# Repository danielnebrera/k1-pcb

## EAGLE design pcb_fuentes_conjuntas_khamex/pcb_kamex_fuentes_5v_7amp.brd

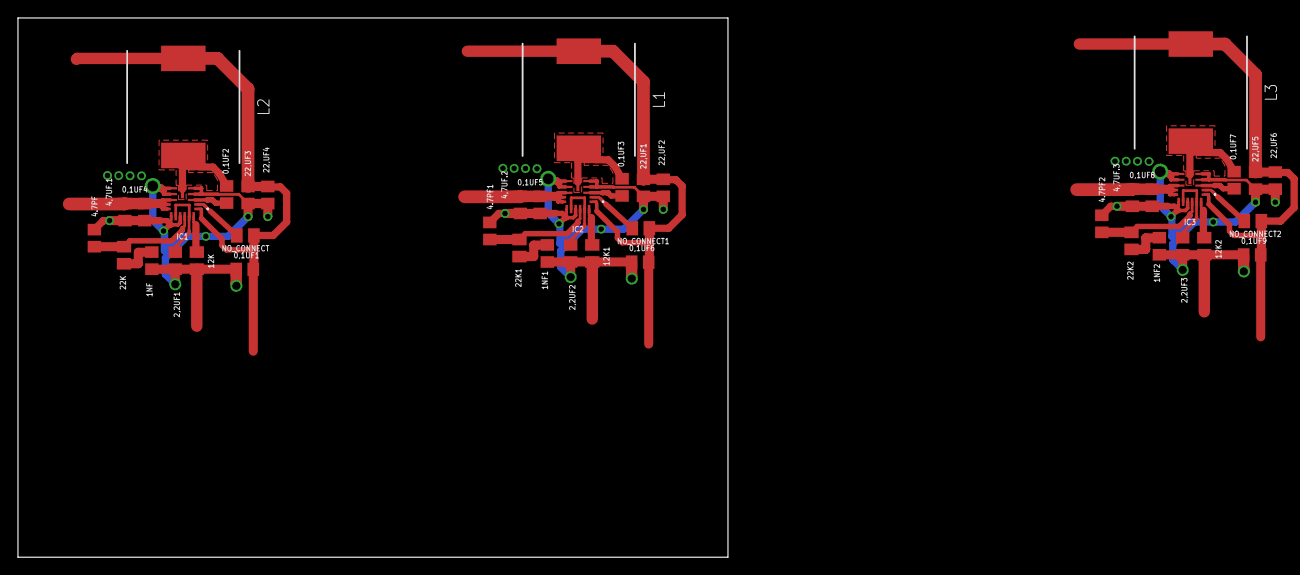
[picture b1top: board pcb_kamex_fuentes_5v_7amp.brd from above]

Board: 2 copper layers, 79.0 x 60.0 mm, 42 parts (0 on the bottom side), 26 nets.

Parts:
0,1UF1, 0,1UF2, 0,1UF3, 0,1UF4, 0,1UF5, 0,1UF6, 0,1UF7, 0,1UF8, 0,1UF9: 0.1uF_50-V; C0805
1NF, 1NF1, 1NF2: 1nf_50-V; C0805
2,2UF1, 2,2UF2, 2,2UF3: 2,2uf_10-V; C0805
4,7UF.1, 4,7UF.2, 4,7UF.3: 4,7uf_50-V; C0805
4.7PF, 4.7PF1, 4.7PF2: 4.7pf_50-V; C0805
12K, 12K1, 12K2: 12k_50v; M0805
22,UF1, 22,UF2, 22,UF3, 22,UF4, 22,UF5, 22,UF6: 22uf_10-V; C0805
22K, 22K1, 22K2: 22k_50v; M0805
IC1, IC2, IC3: MAX20008AFOC_VY+T; MAX20008AFOCVYT
L1, L2, L3: DR125-1R0-R; INDPM125125X600N
NO_CONNECT, NO_CONNECT1, NO_CONNECT2: 10k_50-V; M0805

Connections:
BIAS: 2,2UF1.1, IC1.13, IC1.16
BIAS1: 2,2UF2.1, IC2.13, IC2.16
BIAS2: 2,2UF3.1, IC3.13, IC3.16
BST: 0,1UF2.2, IC1.3
BST1: 0,1UF3.2, IC2.3
BST2: 0,1UF7.2, IC3.3
COM: 4.7PF.1, 22K.1, IC1.15
COM1: 4.7PF1.1, 22K1.1, IC2.15
COM2: 4.7PF2.1, 22K2.1, IC3.15
GND: 0,1UF1.1, 0,1UF4.1, 0,1UF5.1, 0,1UF6.1, 0,1UF8.1, 0,1UF9.1, 1NF.1, 1NF1.1, 1NF2.1, 2,2UF1.2, 2,2UF2.2, 2,2UF3.2, 4,7UF.1.1, 4,7UF.2.1, 4,7UF.3.1, 4.7PF.2, 4.7PF1.2, 4.7PF2.2, 12K.2, 12K1.2, 12K2.2, 22,UF1.1, 22,UF2.1, 22,UF3.1, 22,UF4.1, 22,UF5.1, 22,UF6.1, IC1.4, IC1.5, IC1.7, IC1.8, IC1.12, IC1.14, IC2.4, IC2.5, IC2.7, IC2.8, IC2.12, IC2.14, IC3.4, IC3.5, IC3.7, IC3.8, IC3.12, IC3.14
unnamed: 12K1.1, IC2.17
unnamed: 1NF.2, 22K.2
unnamed: 0,1UF3.1, IC2.6, L1.1
unnamed: IC2.2, NO_CONNECT1.1
unnamed: 1NF1.2, 22K1.2
unnamed: 12K.1, IC1.17
unnamed: 12K2.1, IC3.17
unnamed: 0,1UF7.1, IC3.6, L3.1
unnamed: 0,1UF2.1, IC1.6, L2.1
unnamed: IC1.2, NO_CONNECT.1
unnamed: IC3.2, NO_CONNECT2.1
unnamed: 1NF2.2, 22K2.2
VIN_12V: 0,1UF4.2, 0,1UF5.2, 0,1UF8.2, 4,7UF.1.2, 4,7UF.2.2, 4,7UF.3.2, IC1.9, IC1.10, IC1.11, IC2.9, IC2.10, IC2.11, IC3.9, IC3.10, IC3.11
VOUT_5V: 0,1UF1.2, 22,UF3.2, 22,UF4.2, IC1.1, L2.2, NO_CONNECT.2
VOUT_5V1: 0,1UF6.2, 22,UF1.2, 22,UF2.2, IC2.1, L1.2, NO_CONNECT1.2
VOUT_5V2: 0,1UF9.2, 22,UF5.2, 22,UF6.2, IC3.1, L3.2, NO_CONNECT2.2

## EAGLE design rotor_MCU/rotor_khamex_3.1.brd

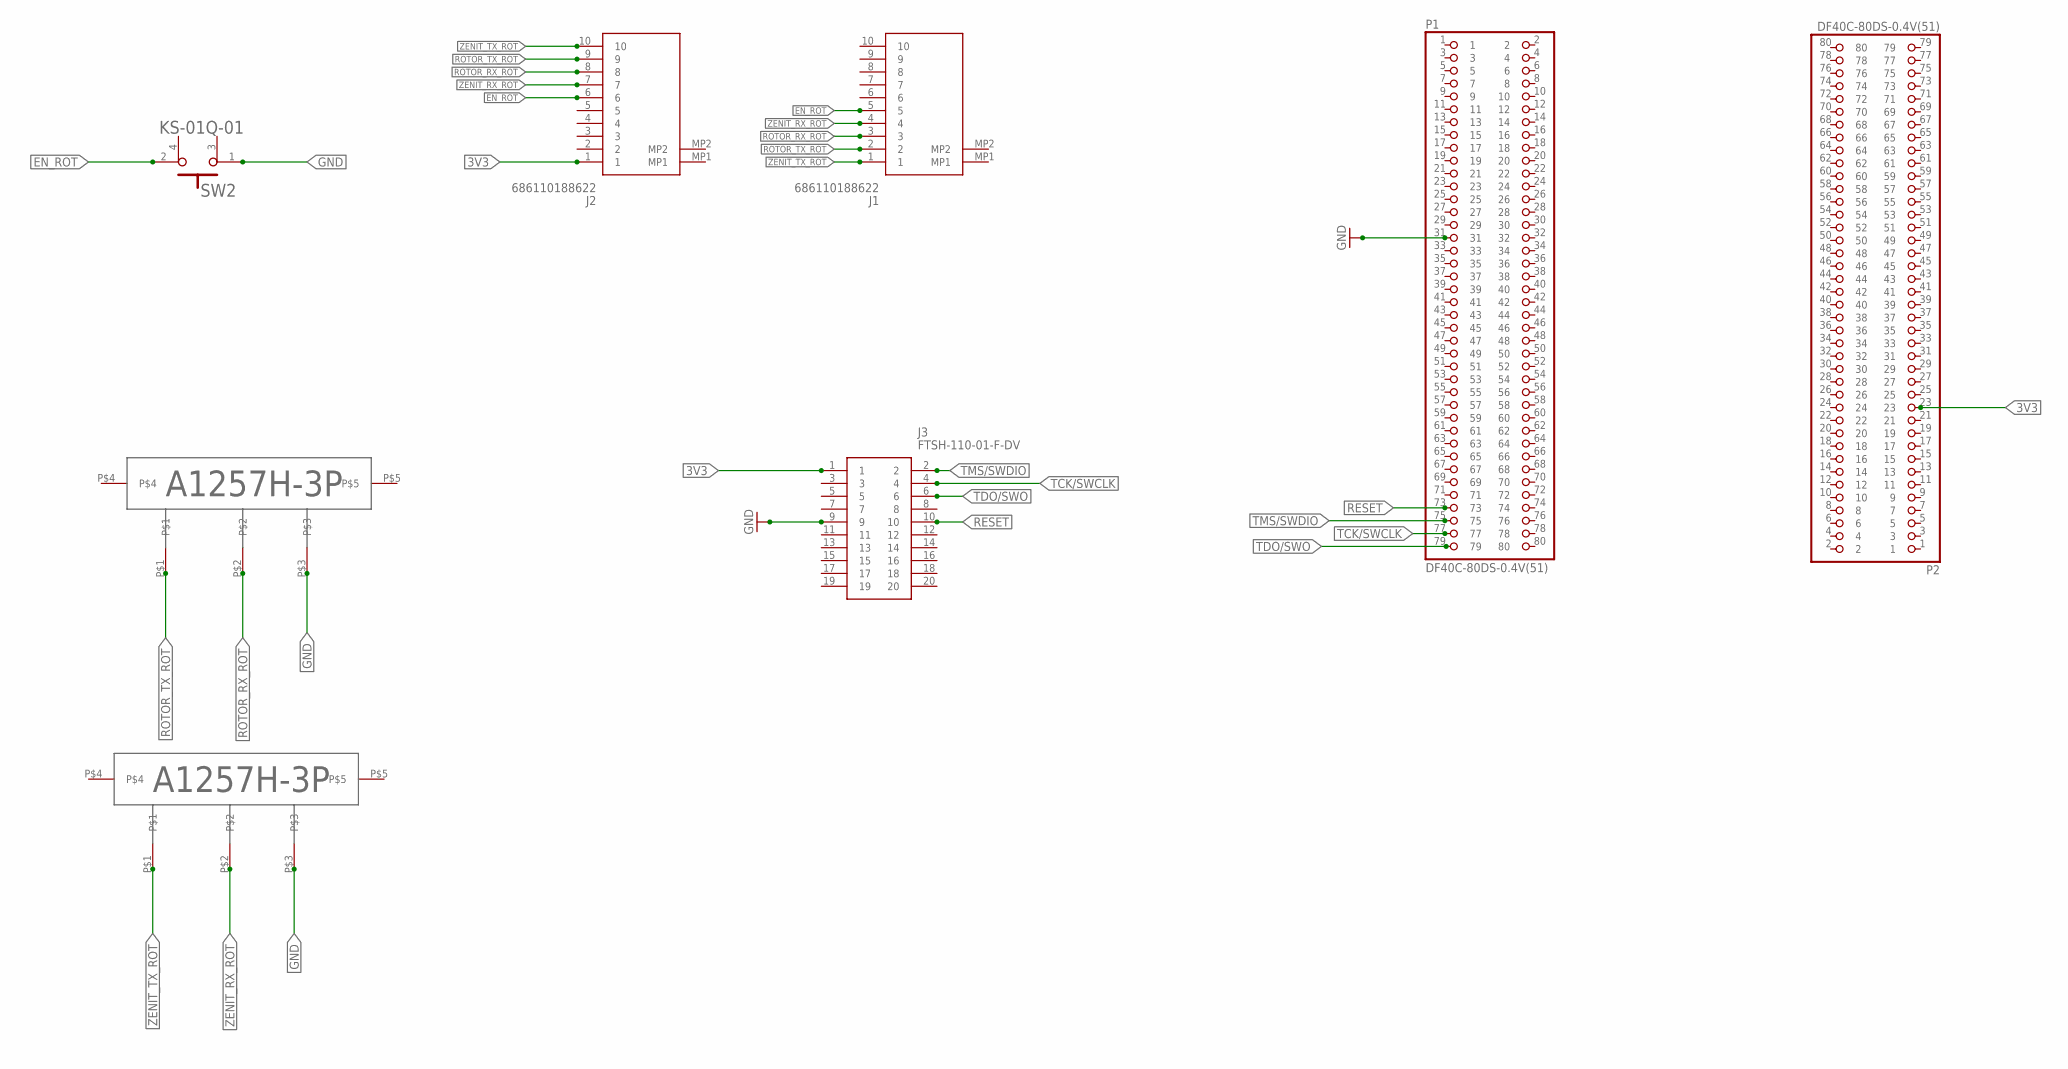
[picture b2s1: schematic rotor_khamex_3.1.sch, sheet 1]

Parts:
J1, J2: 686110188622
J3: FTSH-110-01-F-DV; FTSH-110-XX-YYY-DV
MOTOR_ROTOR: A1257H-3P_DEVICE; A1257H-3P_PACK
MOTOR_ZENIT: A1257H-3P_DEVICE; A1257H-3P_PACK
P1, P2: DF40C-80DS-0.4V(51); HRS_DF40C-80DS-0.4V(51)
SW2: E-SWITCH_KS-01Q-01E-SWITCH_KS-01Q-01_0_0; E-SWITCH_KS-01Q-01_0

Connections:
3V3: J2.1, J3.1, P2.23
EN_ROT: J1.5, J2.6, SW2.2
GND: J3.9, MOTOR_ROTOR.P$3, MOTOR_ZENIT.P$3, P1.31, SW2.1; also elsewhere on the board
RESET: J3.10, P1.73
ROTOR_RX_ROT: J1.3, J2.8, MOTOR_ROTOR.P$2
ROTOR_TX_ROT: J1.2, J2.9, MOTOR_ROTOR.P$1
TCK/SWCLK: J3.4, P1.77
TDO/SWO: J3.6
TMS/SWDIO: J3.2, P1.75
ZENIT_RX_ROT: J1.4, J2.7, MOTOR_ZENIT.P$2
ZENIT_TX_ROT: J1.1, J2.10, MOTOR_ZENIT.P$1

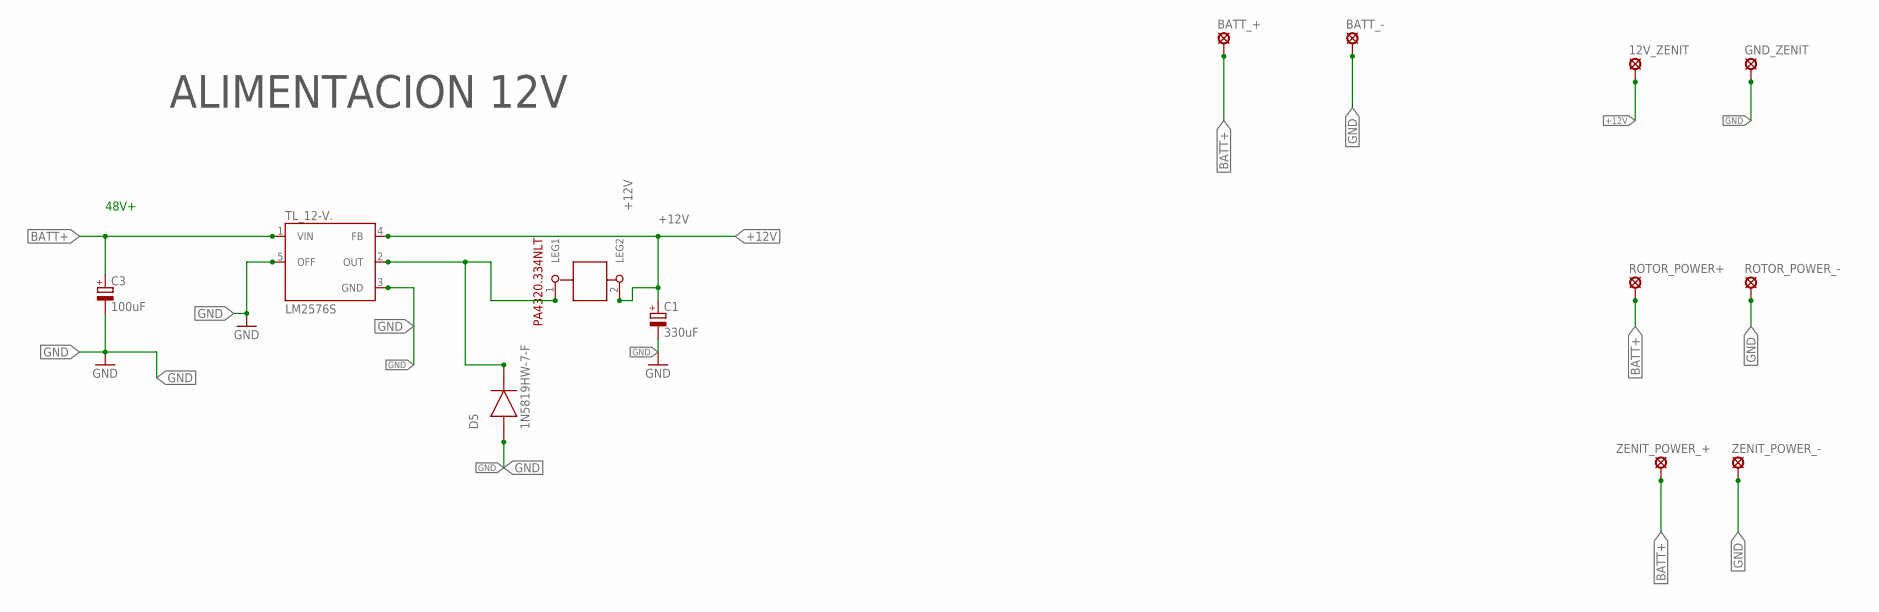
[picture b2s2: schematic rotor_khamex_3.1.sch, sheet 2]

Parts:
12V_ZENIT: SE14
BATT_+: SE14
BATT_-: SE14
C1: 330uF; E5-10,5
C3: 100uF; E5-10,5
D5: 1N5819HW-7-F; SOD370155X135
GND_ZENIT: SE14
L: 1212; 1212SMDINDUCTORPACK
ROTOR_POWER+: SE14
ROTOR_POWER_-: SE14
TL_12-V.: LM2576S; TO263-5
ZENIT_POWER_+: SE14
ZENIT_POWER_-: SE14

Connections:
+12V: 12V_ZENIT.MP, C1.+, L.2 (LEG2), TL_12-V..4 (FB)
BATT+: BATT_+.MP, C3.+, ROTOR_POWER+.MP, TL_12-V..1 (VIN), ZENIT_POWER_+.MP
GND: BATT_-.MP, C1.-, C3.-, D5.2 (A), GND_ZENIT.MP, ROTOR_POWER_-.MP, TL_12-V..3 (GND), TL_12-V..5 (OFF), ZENIT_POWER_-.MP; also elsewhere on the board
unnamed: D5.1 (C), L.1 (LEG1), TL_12-V..2 (OUT)

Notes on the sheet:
48V+
ALIMENTACION 12V

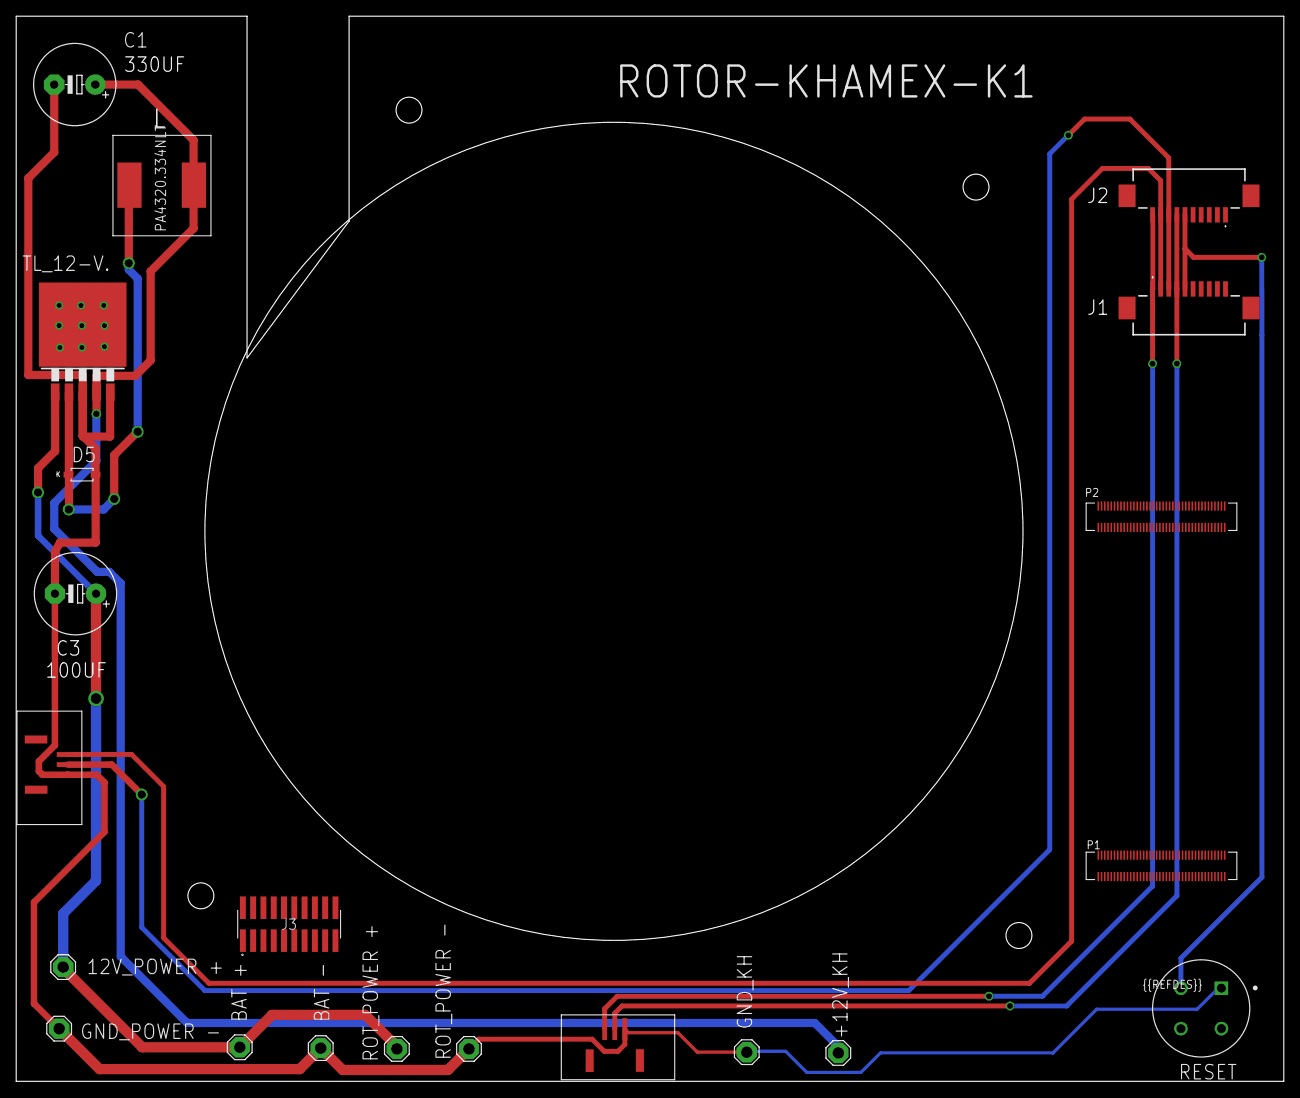
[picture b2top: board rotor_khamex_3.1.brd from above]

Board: 4 copper layers, 156.5 x 131.5 mm, 21 parts (0 on the bottom side), 13 nets.

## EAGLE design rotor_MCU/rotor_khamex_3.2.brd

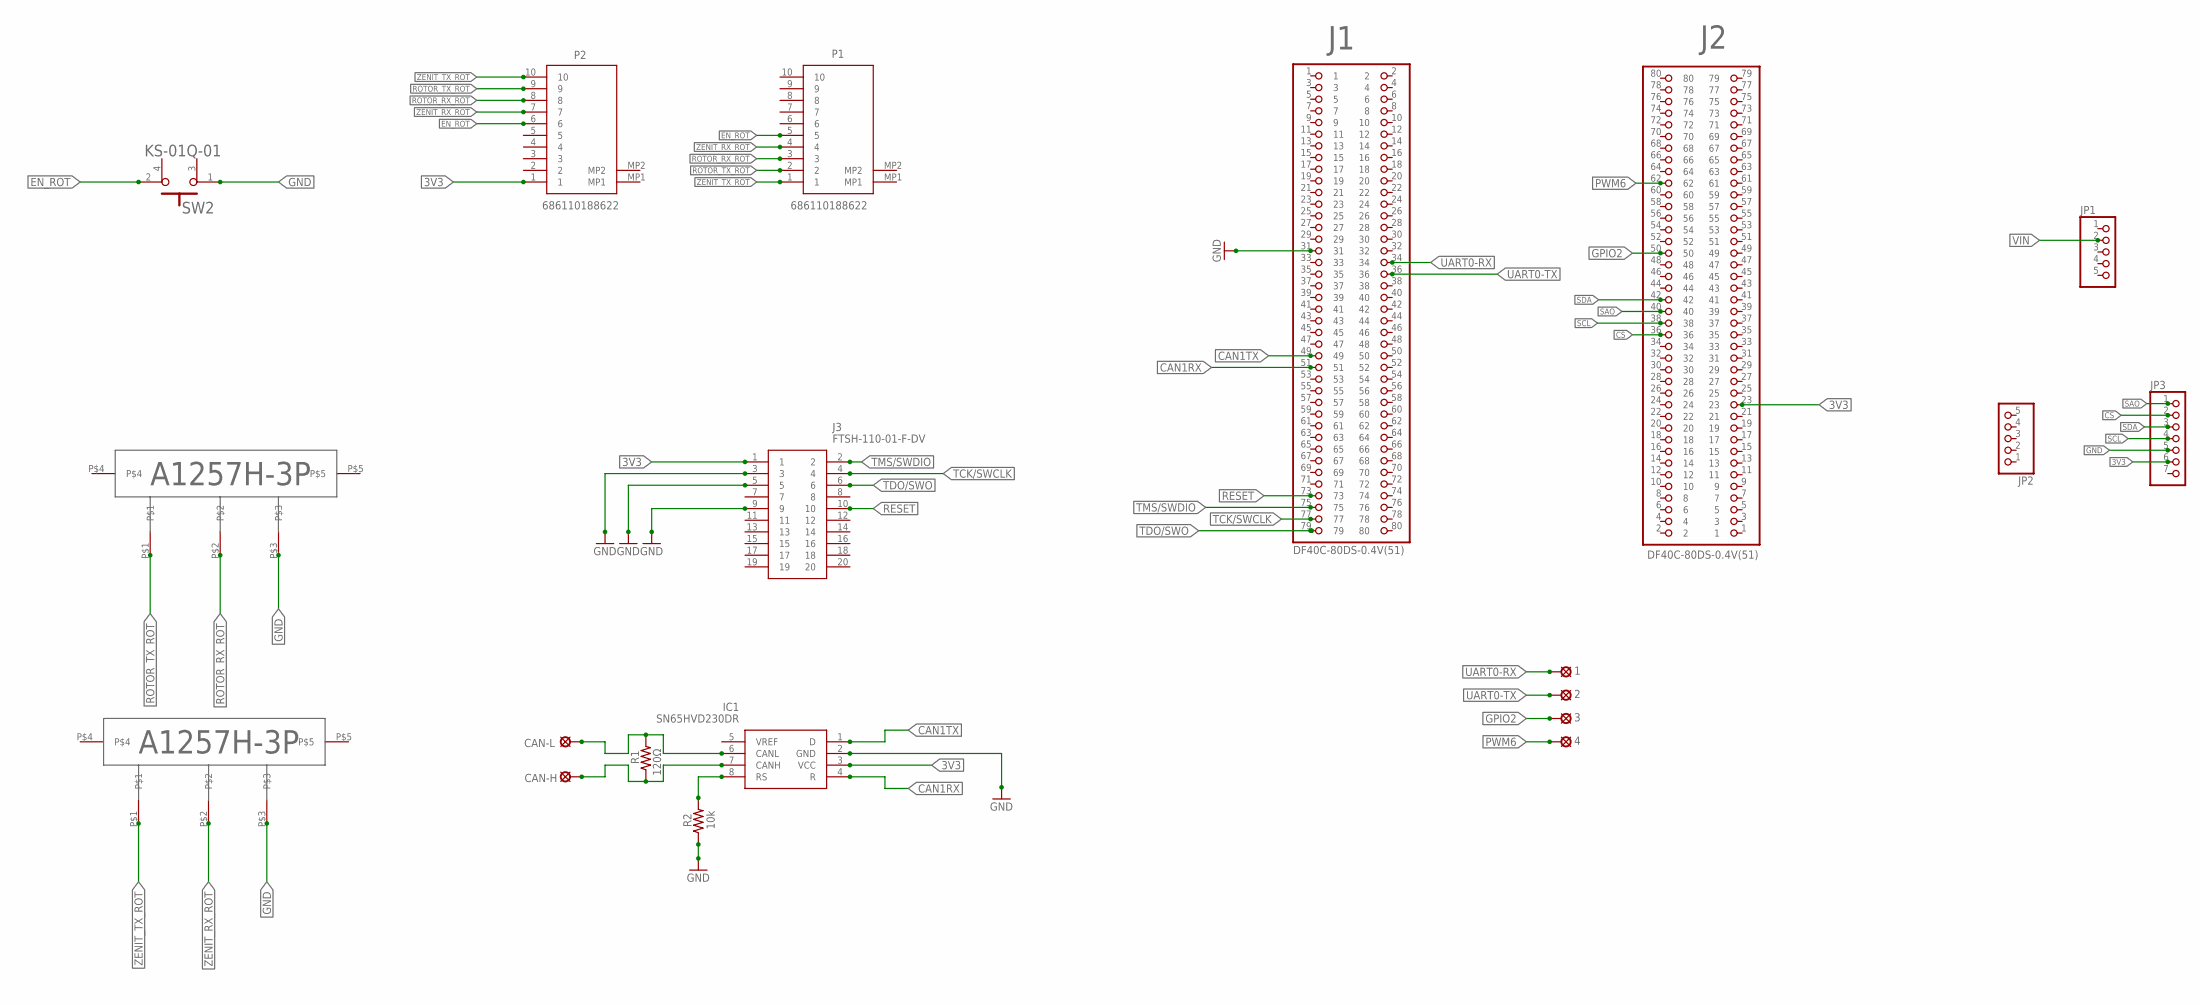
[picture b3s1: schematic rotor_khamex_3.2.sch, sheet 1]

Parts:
1, 2, 3, 4: LSP11
CAN-H: LSP11
CAN-L: LSP11
IC1: SN65HVD230DR; SOT127P600X175-8N
J1, J2: DF40C-80DS-0.4V(51); HRS_DF40C-80DS-0.4V(51)
J3: FTSH-110-01-F-DV; FTSH-110-XX-YYY-DV
JP1, JP2: PINHD-1X5; 1X05
JP3: PINHD-1X7; 1X07
MOTOR_ROTOR: A1257H-3P_DEVICE; A1257H-3P_PACK
MOTOR_ZENIT: A1257H-3P_DEVICE; A1257H-3P_PACK
P1, P2: 686110188622
R1: 120Ω; M0805
R2: 10k; M0805
SW2: E-SWITCH_KS-01Q-01E-SWITCH_KS-01Q-01_0_0; E-SWITCH_KS-01Q-01_0

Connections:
3V3: IC1.3 (VCC), J2.23, J3.1, JP3.6, P2.1
CAN1RX: IC1.4 (R), J1.51
CAN1TX: IC1.1 (D), J1.49
CS: J2.36, JP3.2
EN_ROT: P1.5, P2.6, SW2.2; also elsewhere on the board
GND: IC1.2 (GND), J1.31, J3.3, J3.5, J3.9, JP3.5, MOTOR_ROTOR.P$3, MOTOR_ZENIT.P$3, R2.1, SW2.1; also elsewhere on the board
GPIO2: 3.MP, J2.50
unnamed: CAN-H.MP, IC1.7 (CANH), R1.1
unnamed: CAN-L.MP, IC1.6 (CANL), R1.2
unnamed: IC1.8 (RS), R2.2
PWM6: 4.MP, J2.62
RESET: J1.73, J3.10
ROTOR_RX_ROT: MOTOR_ROTOR.P$2, P1.3, P2.8
ROTOR_TX_ROT: MOTOR_ROTOR.P$1, P1.2, P2.9
SAO: J2.40, JP3.1
SCL: J2.38, JP3.4
SDA: J2.42, JP3.3
TCK/SWCLK: J1.77, J3.4
TDO/SWO: J1.79, J3.6
TMS/SWDIO: J1.75, J3.2
UART0-RX: 1.MP, J1.34
UART0-TX: 2.MP, J1.36
VIN: JP1.2
ZENIT_RX_ROT: MOTOR_ZENIT.P$2, P1.4, P2.7
ZENIT_TX_ROT: MOTOR_ZENIT.P$1, P1.1, P2.10

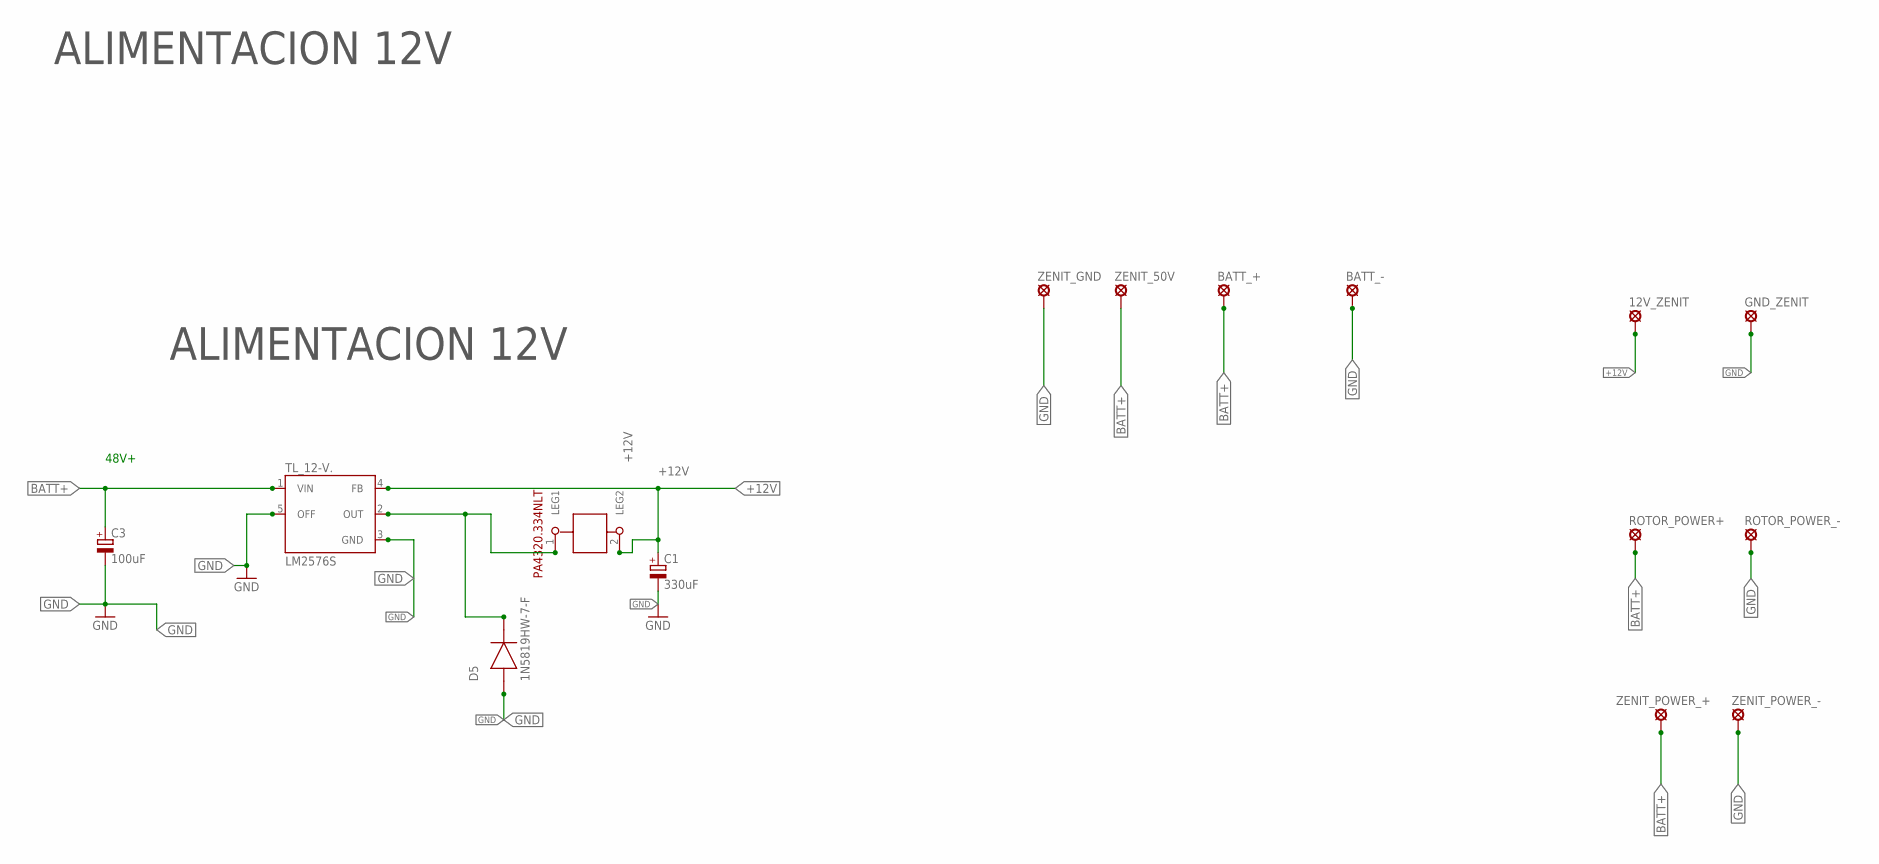
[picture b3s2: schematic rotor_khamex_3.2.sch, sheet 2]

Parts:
12V_ZENIT: SE14
BATT_+: SE14
BATT_-: SE14
C1: 330uF; E5-10,5
C3: 100uF; E5-10,5
D5: 1N5819HW-7-F; SOD370155X135
GND_ZENIT: SE14
L: 1212; 1212SMDINDUCTORPACK
ROTOR_POWER+: SE14
ROTOR_POWER_-: SE14
TL_12-V.: LM2576S; TO263-5
ZENIT_50V: SE14
ZENIT_GND: SE14
ZENIT_POWER_+: SE14
ZENIT_POWER_-: SE14

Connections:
+12V: 12V_ZENIT.MP, C1.+, L.2 (LEG2), TL_12-V..4 (FB); also elsewhere on the board
BATT+: BATT_+.MP, C3.+, ROTOR_POWER+.MP, TL_12-V..1 (VIN), ZENIT_50V.MP, ZENIT_POWER_+.MP
GND: BATT_-.MP, C1.-, C3.-, D5.2 (A), GND_ZENIT.MP, ROTOR_POWER_-.MP, TL_12-V..3 (GND), TL_12-V..5 (OFF), ZENIT_GND.MP, ZENIT_POWER_-.MP; also elsewhere on the board
unnamed: D5.1 (C), L.1 (LEG1), TL_12-V..2 (OUT)

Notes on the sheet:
48V+
ALIMENTACION 12V

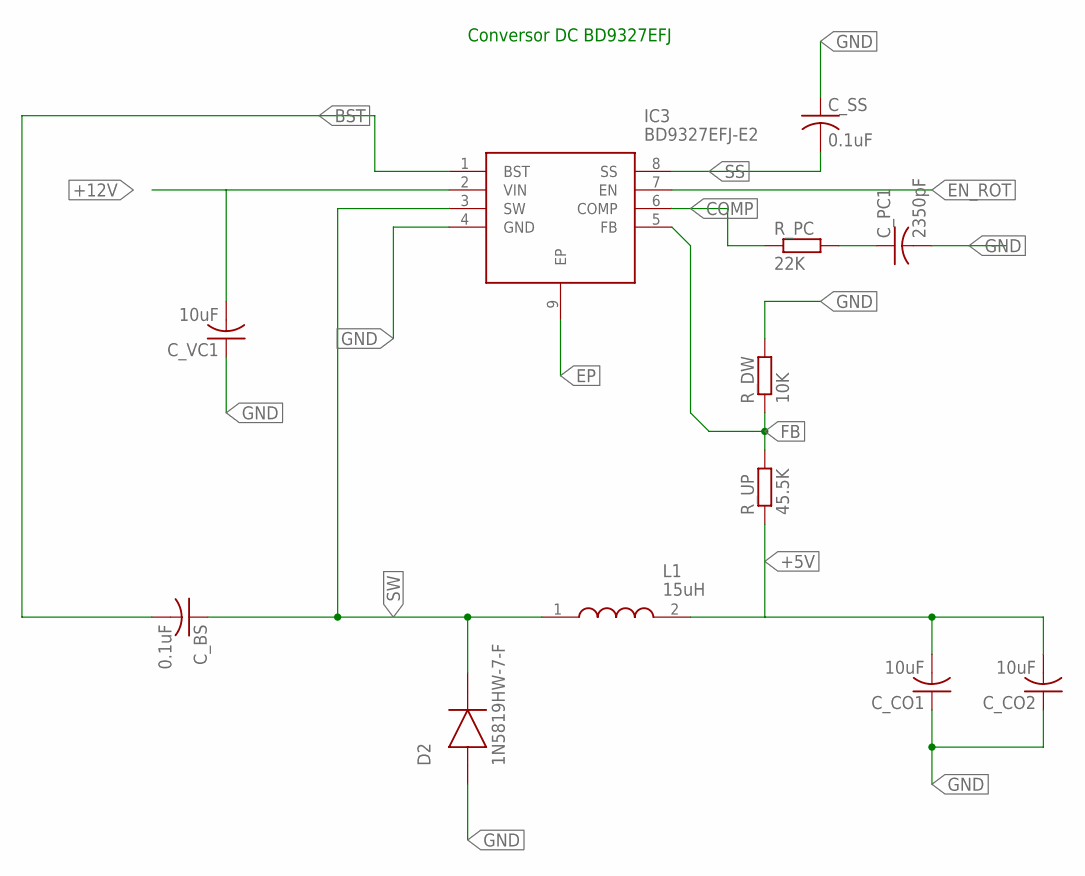
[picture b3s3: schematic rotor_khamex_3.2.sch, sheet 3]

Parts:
C_BS: 0.1uF; C0805
C_CO1, C_CO2: 10uF; C0805
C_PC1: 2350pF; C0805
C_SS: 0.1uF; C0805
C_VC1: 10uF; C0805
D2: 1N5819HW-7-F; SOD370155X135
IC3: BD9327EFJ-E2; SOIC127P600X100-9N
L1: 15uH; SRP06126R8K
R_DW: 10K; M0805
R_PC: 22K; M0805
R_UP: 45.5K; M0805

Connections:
+5V: C_CO1.2, C_CO2.2, L1.2, R_UP.1
+12V: C_VC1.2, IC3.2 (VIN); also elsewhere on the board
BST: C_BS.2, IC3.1 (BST)
COMP: IC3.6 (COMP), R_PC.1
EN_ROT: IC3.7 (EN); also elsewhere on the board
EP: IC3.9 (EP)
FB: IC3.5 (FB), R_DW.1, R_UP.2
GND: C_CO1.1, C_CO2.1, C_PC1.2, C_SS.1, C_VC1.1, D2.2 (A), IC3.4 (GND), R_DW.2; also elsewhere on the board
unnamed: C_PC1.1, R_PC.2
SS: C_SS.2, IC3.8 (SS)
SW: C_BS.1, D2.1 (C), IC3.3 (SW), L1.1

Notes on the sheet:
Conversor DC BD9327EFJ

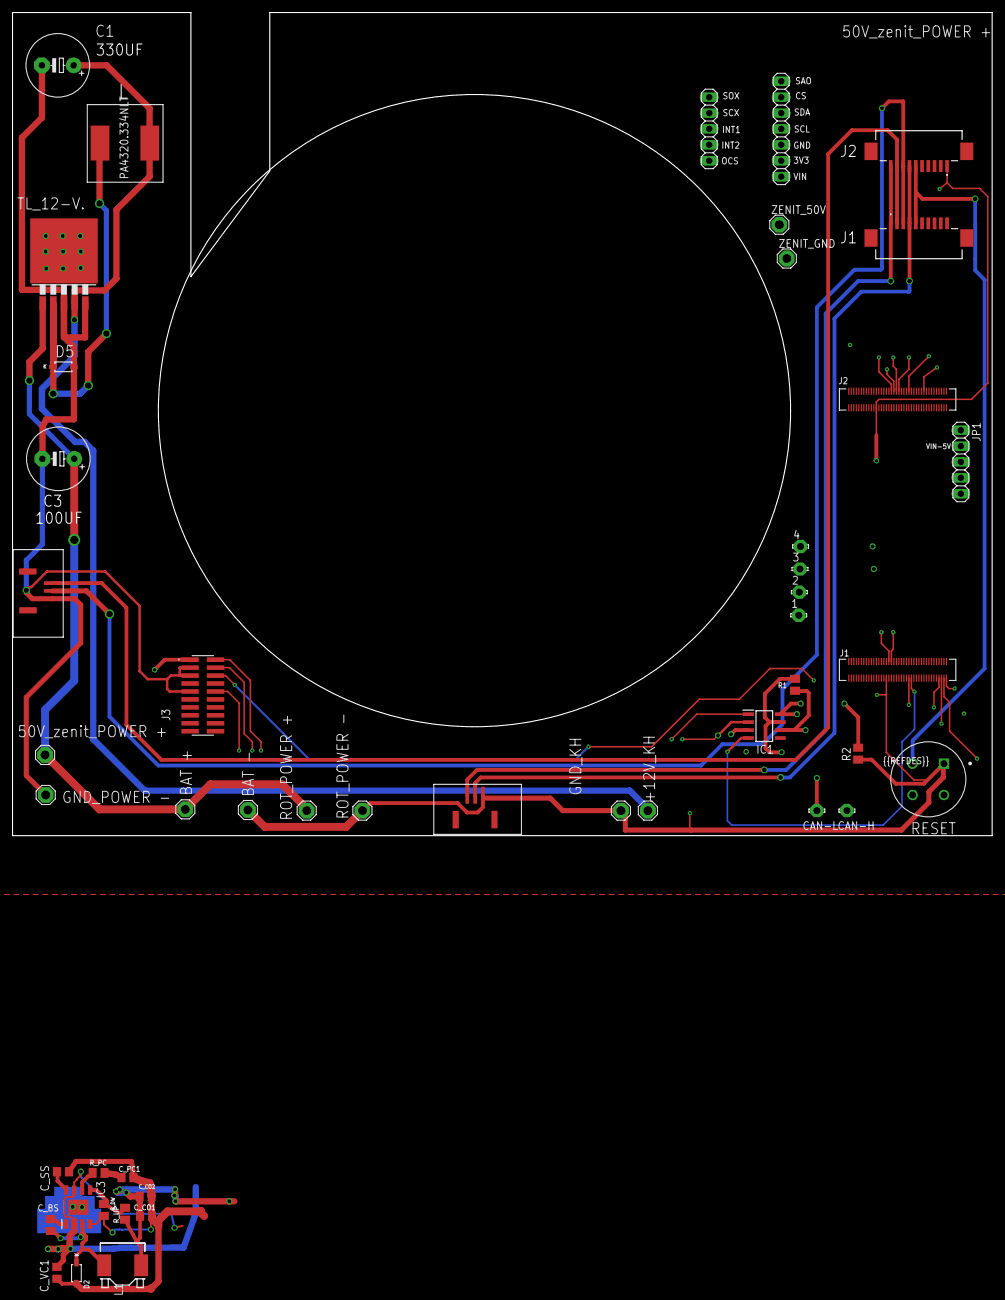
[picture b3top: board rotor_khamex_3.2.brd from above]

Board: 4 copper layers, 156.5 x 131.5 mm, 47 parts (0 on the bottom side), 34 nets.
